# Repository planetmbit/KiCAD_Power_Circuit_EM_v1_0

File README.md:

# KiCAD_Power_Circuit_EM_v1_0
This is the Power Circuit of Private Satellite EM(Engineering Model)'s KiCAD Repository (This belongs to the author and The Ryman Sat Project.)

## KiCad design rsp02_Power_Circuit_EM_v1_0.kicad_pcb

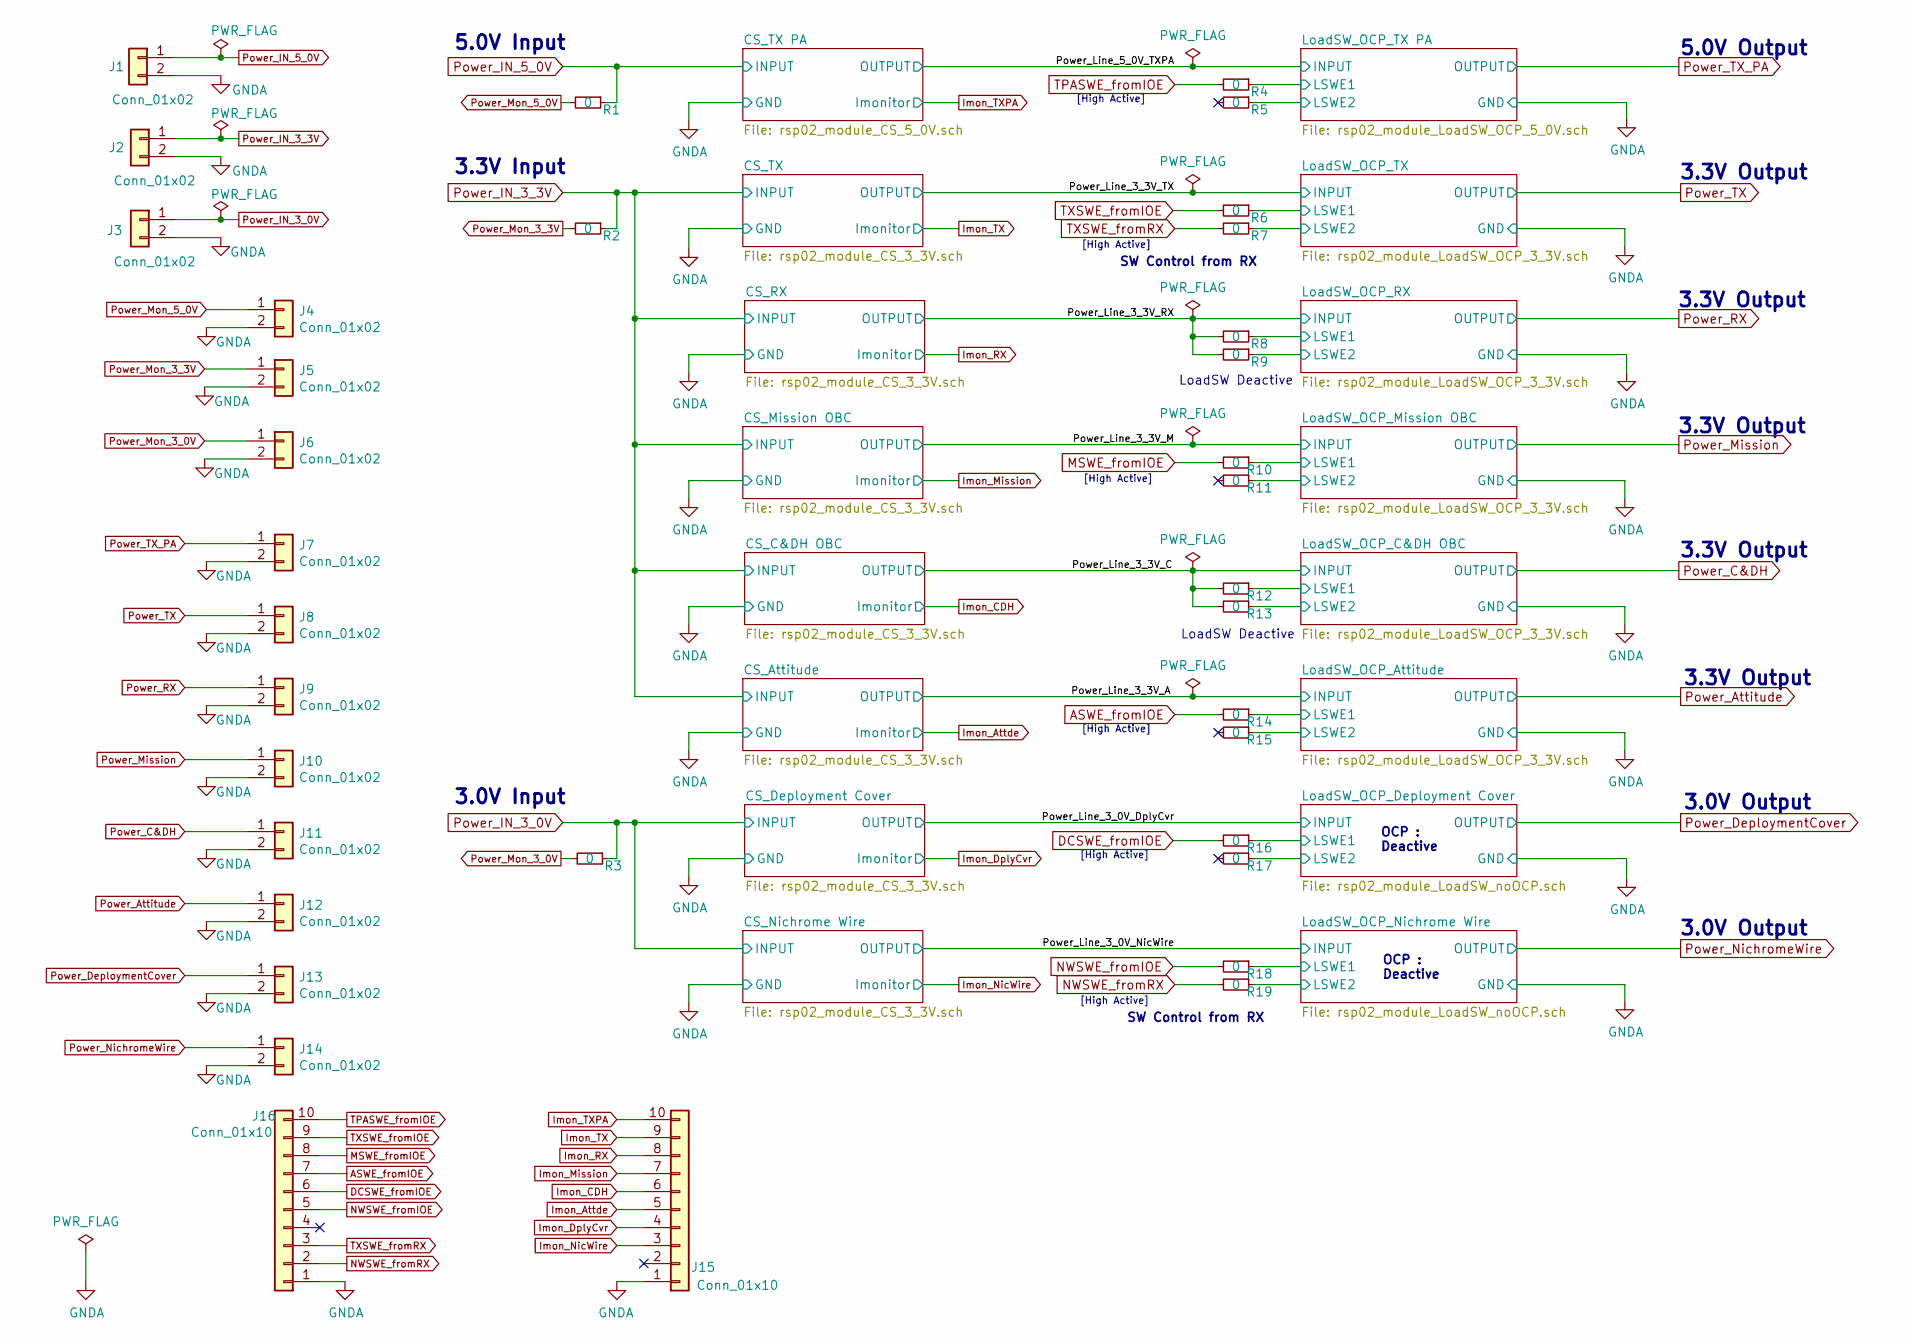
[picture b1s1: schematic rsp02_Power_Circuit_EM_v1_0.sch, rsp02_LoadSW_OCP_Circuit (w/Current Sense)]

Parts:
J1, J2, J3, J7, J8, J9, J10, J11, J12, J13, J14: Conn_01x02; TerminalBlock_Phoenix_MKDS-3-2-5.08_1x02_P5.08mm_Horizontal
J4, J5, J6: Conn_01x02; PinHeader_1x02_P2.54mm_Vertical
J15: Conn_01x10; PinHeader_1x10_P2.54mm_Vertical
J16: Conn_01x10; TerminalBlock_Phoenix_MKDS-3-10-5.08_1x10_P5.08mm_Horizontal
R1, R2, R3, R4, R5, R6, R7, R8, R9, R10, R11, R12, R13, R14, R15, R16, R17, R18, R19: 0; R_0603_1608Metric

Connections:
/LoadSW_OCP_Attitude/LSWE1: R14.1; also elsewhere on the board
/LoadSW_OCP_Attitude/LSWE2: R15.1; also elsewhere on the board
/LoadSW_OCP_C&DH OBC/LSWE1: R12.1; also elsewhere on the board
/LoadSW_OCP_C&DH OBC/LSWE2: R13.1; also elsewhere on the board
/LoadSW_OCP_Deployment Cover/LSWE1: R16.1; also elsewhere on the board
/LoadSW_OCP_Deployment Cover/LSWE2: R17.1; also elsewhere on the board
/LoadSW_OCP_Mission OBC/LSWE1: R10.1; also elsewhere on the board
/LoadSW_OCP_Mission OBC/LSWE2: R11.1; also elsewhere on the board
/LoadSW_OCP_Nichrome Wire/LSWE1: R18.1; also elsewhere on the board
/LoadSW_OCP_Nichrome Wire/LSWE2: R19.1; also elsewhere on the board
/LoadSW_OCP_RX/LSWE1: R8.1; also elsewhere on the board
/LoadSW_OCP_RX/LSWE2: R9.1; also elsewhere on the board
/LoadSW_OCP_TX PA/LSWE1: R4.1; also elsewhere on the board
/LoadSW_OCP_TX PA/LSWE2: R5.1; also elsewhere on the board
/LoadSW_OCP_TX/LSWE1: R6.1; also elsewhere on the board
/LoadSW_OCP_TX/LSWE2: R7.1; also elsewhere on the board
/Power_Line_3_3V_C: R12.2, R13.2; also elsewhere on the board
/Power_Line_3_3V_RX: R8.2, R9.2; also elsewhere on the board
ASWE_fromIOE: J16.7, R14.2
DCSWE_fromIOE: J16.6, R16.2
GNDA: J1.2, J2.2, J3.2, J4.2, J5.2, J6.2, J7.2, J8.2, J9.2, J10.2, J11.2, J12.2, J13.2, J14.2, J15.1, J16.1; also elsewhere on the board
Imon_Attde: J15.5; also elsewhere on the board
Imon_CDH: J15.6; also elsewhere on the board
Imon_DplyCvr: J15.4; also elsewhere on the board
Imon_Mission: J15.7; also elsewhere on the board
Imon_NicWire: J15.3; also elsewhere on the board
Imon_RX: J15.8; also elsewhere on the board
Imon_TX: J15.9; also elsewhere on the board
Imon_TXPA: J15.10; also elsewhere on the board
MSWE_fromIOE: J16.8, R10.2
NWSWE_fromIOE: J16.5, R18.2
NWSWE_fromRX: J16.2, R19.2
Power_Attitude: J12.1; also elsewhere on the board
Power_C&DH: J11.1; also elsewhere on the board
Power_DeploymentCover: J13.1; also elsewhere on the board
Power_IN_3_0V: J3.1, R3.1; also elsewhere on the board
Power_IN_3_3V: J2.1, R2.1; also elsewhere on the board
Power_IN_5_0V: J1.1, R1.1; also elsewhere on the board
Power_Mission: J10.1; also elsewhere on the board
Power_Mon_3_0V: J6.1, R3.2
Power_Mon_3_3V: J5.1, R2.2
Power_Mon_5_0V: J4.1, R1.2
Power_NichromeWire: J14.1; also elsewhere on the board
Power_RX: J9.1; also elsewhere on the board
Power_TX: J8.1; also elsewhere on the board
Power_TX_PA: J7.1; also elsewhere on the board
TPASWE_fromIOE: J16.10, R4.2
TXSWE_fromIOE: J16.9, R6.2
TXSWE_fromRX: J16.3, R7.2

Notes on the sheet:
5.0V Output
3.3V Output
OCP : Deactive
LoadSW Deactive
3.0V Output
SW Control from RX
[High Active]
3.0V Input
3.3V Input
5.0V Input

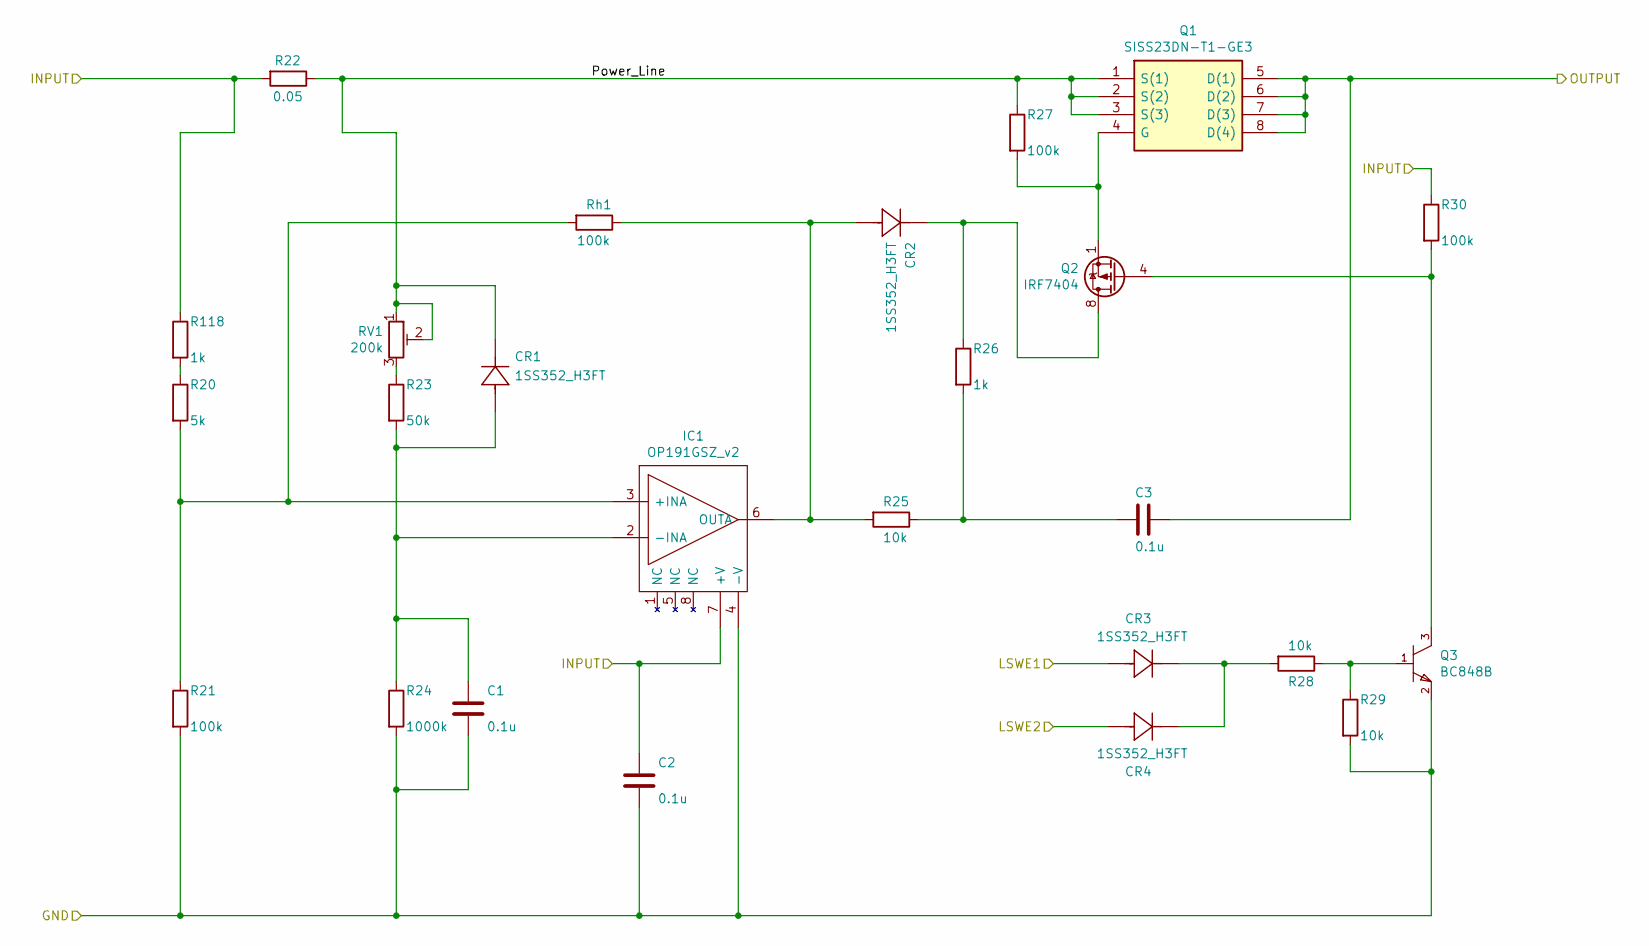
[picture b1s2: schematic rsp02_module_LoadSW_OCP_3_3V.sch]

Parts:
C16, C17, C18: 0.1u; C_0603_1608Metric
CR23, CR24, CR25, CR26: 1SS352_H3FT
IC6: OP191GSZ_v2; SOIC-8_3.9x4.9mm_P1.27mm; Manufacturer_Part_Number OP191GSZ
Q19: SISS23DN-T1-GE3; POWERPAK-1212-8; Manufacturer_Part_Number SISS23DN-T1-GE3
Q20: IRF7404; SOIC-8_3.9x4.9mm_P1.27mm
Q21: BC848B; SOT-23; mouser part number 771-BC848B215; digikey description TRANS NPN 30V 0.1A SOT23
R79: 5k; R_0603_1608Metric
R80, R86, R89: 100k; R_0603_1608Metric
R81: 0.05; R_2512_6332Metric
R82: 50k; R_0603_1608Metric
R83: 1000k; R_0603_1608Metric
R84, R87, R88: 10k; R_0603_1608Metric
R85, R123: 1k; R_0603_1608Metric
RV6: 200k; Potentiometer_Bourns_3314G_Vertical
Rh6: 100k; R_0603_1608Metric

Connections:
/LoadSW_OCP_TX/LSWE1: CR25.2 (anode); also elsewhere on the board
/LoadSW_OCP_TX/LSWE2: CR26.2 (anode); also elsewhere on the board
/LoadSW_OCP_TX/Power_Line: CR23.1 (cathode), Q19.1 (S(1)), Q19.2 (S(2)), Q19.3 (S(3)), R81.1, R86.1, RV6.1, RV6.2
/Power_Line_3_3V_TX: C17.1, IC6.7 (+V), R81.2, R89.1, R123.1; also elsewhere on the board
GNDA: C16.2, C17.2, IC6.4 (-V), Q21.2 (emitter), R80.2, R83.2, R88.2; also elsewhere on the board
unnamed: C16.1, CR23.2 (anode), IC6.2 (-INA), R82.2, R83.1
unnamed: C18.2, R84.1, R85.2
unnamed: CR24.1 (cathode), Q20.5 (D), Q20.6 (D), Q20.7 (D), Q20.8 (D), R85.1
unnamed: CR24.2 (anode), IC6.6 (OUTA), R84.2, Rh6.1
unnamed: CR25.1 (cathode), CR26.1 (cathode), R87.2
unnamed: IC6.3 (+INA), R79.2, R80.1, Rh6.2
unnamed: Q19.4 (G), Q20.1 (S), Q20.2 (S), Q20.3 (S), R86.2
unnamed: Q20.4 (G), Q21.3 (collector), R89.2
unnamed: Q21.1 (base), R87.1, R88.1
unnamed: R82.1, RV6.3
unnamed: R79.1, R123.2
Power_TX: C18.1, Q19.5 (D(1)), Q19.6 (D(2)), Q19.7 (D(3)), Q19.8 (D(4)); also elsewhere on the board

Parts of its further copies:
C1, C2, C3, C4, C5, C6, C7, C8, C9, C10, C11, C12: 0.1u; C_0603_1608Metric
CR1, CR2, CR3, CR4, CR5, CR6, CR7, CR8, CR9, CR10, CR11, CR12, CR13, CR14, CR15, CR16: 1SS352_H3FT
IC1, IC2, IC3, IC4: OP191GSZ_v2; SOIC-8_3.9x4.9mm_P1.27mm; Manufacturer_Part_Number OP191GSZ
Q1, Q4, Q7, Q10: SISS23DN-T1-GE3; POWERPAK-1212-8; Manufacturer_Part_Number SISS23DN-T1-GE3
Q2, Q5, Q8, Q11: IRF7404; SOIC-8_3.9x4.9mm_P1.27mm
Q3, Q6, Q9, Q12: BC848B; SOT-23; mouser part number 771-BC848B215; digikey description TRANS NPN 30V 0.1A SOT23
R20, R31, R42, R53: 5k; R_0603_1608Metric
R21, R27, R30, R32, R38, R41, R43, R49, R52, R54, R60, R63: 100k; R_0603_1608Metric
R22, R33, R44, R55: 0.05; R_2512_6332Metric
R23, R34, R45, R56: 50k; R_0603_1608Metric
R24, R35, R46, R57: 1000k; R_0603_1608Metric
R25, R28, R29, R36, R39, R40, R47, R50, R51, R58, R61, R62: 10k; R_0603_1608Metric
R26, R37, R48, R59, R118, R119, R120, R121: 1k; R_0603_1608Metric
RV1, RV2, RV3, RV4: 200k; Potentiometer_Bourns_3314G_Vertical
Rh1, Rh2, Rh3, Rh4: 100k; R_0603_1608Metric

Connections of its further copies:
/LoadSW_OCP_Attitude/LSWE1: CR15.2 (anode); also elsewhere on the board
/LoadSW_OCP_Attitude/LSWE2: CR16.2 (anode); also elsewhere on the board
/LoadSW_OCP_Attitude/Power_Line: CR13.1 (cathode), Q10.1 (S(1)), Q10.2 (S(2)), Q10.3 (S(3)), R55.1, R60.1, RV4.1, RV4.2
/LoadSW_OCP_C&DH OBC/LSWE1: CR11.2 (anode); also elsewhere on the board
/LoadSW_OCP_C&DH OBC/LSWE2: CR12.2 (anode); also elsewhere on the board
/LoadSW_OCP_C&DH OBC/Power_Line: CR9.1 (cathode), Q7.1 (S(1)), Q7.2 (S(2)), Q7.3 (S(3)), R44.1, R49.1, RV3.1, RV3.2
/LoadSW_OCP_Mission OBC/LSWE1: CR7.2 (anode); also elsewhere on the board
/LoadSW_OCP_Mission OBC/LSWE2: CR8.2 (anode); also elsewhere on the board
/LoadSW_OCP_Mission OBC/Power_Line: CR5.1 (cathode), Q4.1 (S(1)), Q4.2 (S(2)), Q4.3 (S(3)), R33.1, R38.1, RV2.1, RV2.2
/LoadSW_OCP_RX/LSWE1: CR3.2 (anode); also elsewhere on the board
/LoadSW_OCP_RX/LSWE2: CR4.2 (anode); also elsewhere on the board
/LoadSW_OCP_RX/Power_Line: CR1.1 (cathode), Q1.1 (S(1)), Q1.2 (S(2)), Q1.3 (S(3)), R22.1, R27.1, RV1.1, RV1.2
/Power_Line_3_3V_A: C11.1, IC4.7 (+V), R55.2, R63.1, R121.1; also elsewhere on the board
/Power_Line_3_3V_C: C8.1, IC3.7 (+V), R44.2, R52.1, R120.1; also elsewhere on the board
/Power_Line_3_3V_M: C5.1, IC2.7 (+V), R33.2, R41.1, R119.1; also elsewhere on the board
/Power_Line_3_3V_RX: C2.1, IC1.7 (+V), R22.2, R30.1, R118.1; also elsewhere on the board
GNDA: C1.2, C2.2, C4.2, C5.2, C7.2, C8.2, C10.2, C11.2, IC1.4 (-V), IC2.4 (-V), IC3.4 (-V), IC4.4 (-V), Q3.2 (emitter), Q6.2 (emitter), Q9.2 (emitter), Q12.2 (emitter), R21.2, R24.2, R29.2, R32.2, R35.2, R40.2, R43.2, R46.2, R51.2, R54.2, R57.2, R62.2; also elsewhere on the board
unnamed: C1.1, CR1.2 (anode), IC1.2 (-INA), R23.2, R24.1
unnamed: C3.2, R25.1, R26.2
unnamed: C4.1, CR5.2 (anode), IC2.2 (-INA), R34.2, R35.1
unnamed: C6.2, R36.1, R37.2
unnamed: C7.1, CR9.2 (anode), IC3.2 (-INA), R45.2, R46.1
unnamed: C9.2, R47.1, R48.2
unnamed: C10.1, CR13.2 (anode), IC4.2 (-INA), R56.2, R57.1
unnamed: C12.2, R58.1, R59.2
unnamed: CR2.1 (cathode), Q2.5 (D), Q2.6 (D), Q2.7 (D), Q2.8 (D), R26.1
unnamed: CR2.2 (anode), IC1.6 (OUTA), R25.2, Rh1.1
unnamed: CR3.1 (cathode), CR4.1 (cathode), R28.2
unnamed: CR6.1 (cathode), Q5.5 (D), Q5.6 (D), Q5.7 (D), Q5.8 (D), R37.1
unnamed: CR6.2 (anode), IC2.6 (OUTA), R36.2, Rh2.1
unnamed: CR7.1 (cathode), CR8.1 (cathode), R39.2
unnamed: CR10.1 (cathode), Q8.5 (D), Q8.6 (D), Q8.7 (D), Q8.8 (D), R48.1
unnamed: CR10.2 (anode), IC3.6 (OUTA), R47.2, Rh3.1
unnamed: CR11.1 (cathode), CR12.1 (cathode), R50.2
unnamed: CR14.1 (cathode), Q11.5 (D), Q11.6 (D), Q11.7 (D), Q11.8 (D), R59.1
unnamed: CR14.2 (anode), IC4.6 (OUTA), R58.2, Rh4.1
unnamed: CR15.1 (cathode), CR16.1 (cathode), R61.2
unnamed: IC1.3 (+INA), R20.2, R21.1, Rh1.2
unnamed: IC2.3 (+INA), R31.2, R32.1, Rh2.2
unnamed: IC3.3 (+INA), R42.2, R43.1, Rh3.2
unnamed: IC4.3 (+INA), R53.2, R54.1, Rh4.2
unnamed: Q1.4 (G), Q2.1 (S), Q2.2 (S), Q2.3 (S), R27.2
unnamed: Q2.4 (G), Q3.3 (collector), R30.2
unnamed: Q3.1 (base), R28.1, R29.1
unnamed: Q4.4 (G), Q5.1 (S), Q5.2 (S), Q5.3 (S), R38.2
unnamed: Q5.4 (G), Q6.3 (collector), R41.2
unnamed: Q6.1 (base), R39.1, R40.1
unnamed: Q7.4 (G), Q8.1 (S), Q8.2 (S), Q8.3 (S), R49.2
unnamed: Q8.4 (G), Q9.3 (collector), R52.2
unnamed: Q9.1 (base), R50.1, R51.1
unnamed: Q10.4 (G), Q11.1 (S), Q11.2 (S), Q11.3 (S), R60.2
unnamed: Q11.4 (G), Q12.3 (collector), R63.2
unnamed: Q12.1 (base), R61.1, R62.1
unnamed: R23.1, RV1.3
unnamed: R34.1, RV2.3
unnamed: R45.1, RV3.3
unnamed: R56.1, RV4.3
unnamed: R20.1, R118.2
unnamed: R31.1, R119.2
unnamed: R42.1, R120.2
unnamed: R53.1, R121.2
Power_Attitude: C12.1, Q10.5 (D(1)), Q10.6 (D(2)), Q10.7 (D(3)), Q10.8 (D(4)); also elsewhere on the board
Power_C&DH: C9.1, Q7.5 (D(1)), Q7.6 (D(2)), Q7.7 (D(3)), Q7.8 (D(4)); also elsewhere on the board
Power_Mission: C6.1, Q4.5 (D(1)), Q4.6 (D(2)), Q4.7 (D(3)), Q4.8 (D(4)); also elsewhere on the board
Power_RX: C3.1, Q1.5 (D(1)), Q1.6 (D(2)), Q1.7 (D(3)), Q1.8 (D(4)); also elsewhere on the board

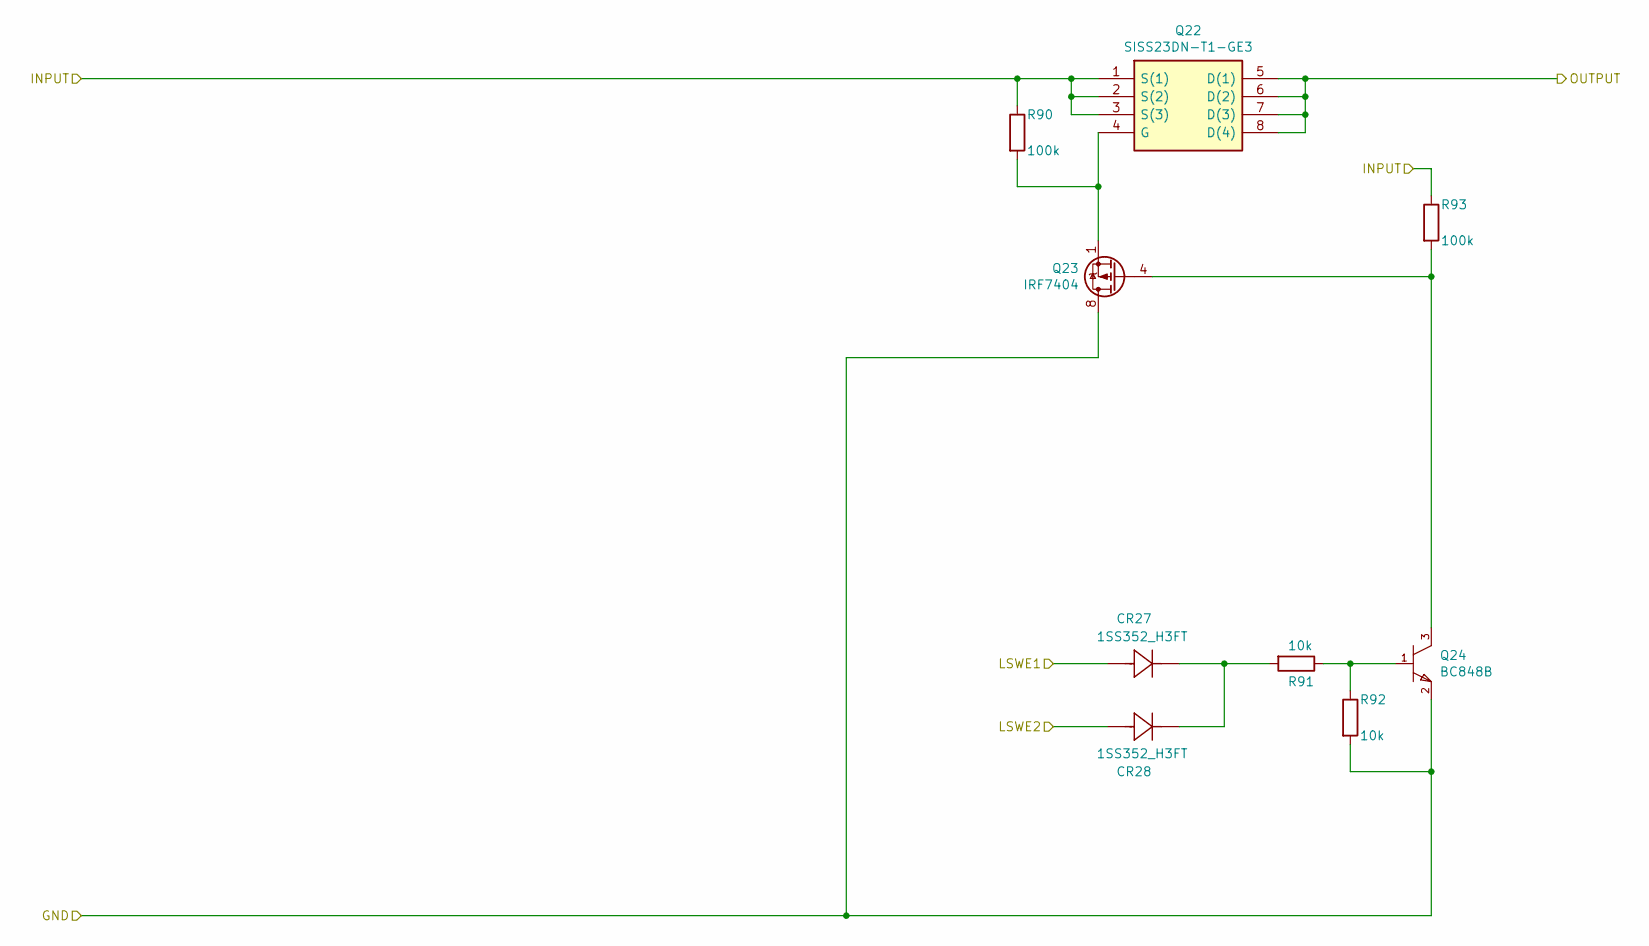
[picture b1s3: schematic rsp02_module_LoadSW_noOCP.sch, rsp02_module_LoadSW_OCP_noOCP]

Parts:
CR27, CR28: 1SS352_H3FT
Q22: SISS23DN-T1-GE3; POWERPAK-1212-8; Manufacturer_Part_Number SISS23DN-T1-GE3
Q23: IRF7404; SOIC-8_3.9x4.9mm_P1.27mm
Q24: BC848B; SOT-23; mouser part number 771-BC848B215; digikey description TRANS NPN 30V 0.1A SOT23
R90, R93: 100k; R_0603_1608Metric
R91, R92: 10k; R_0603_1608Metric

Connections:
/LoadSW_OCP_Deployment Cover/LSWE1: CR27.2 (anode); also elsewhere on the board
/LoadSW_OCP_Deployment Cover/LSWE2: CR28.2 (anode); also elsewhere on the board
/Power_Line_3_0V_DplyCvr: Q22.1 (S(1)), Q22.2 (S(2)), Q22.3 (S(3)), R90.1, R93.1; also elsewhere on the board
GNDA: Q23.5 (D), Q23.6 (D), Q23.7 (D), Q23.8 (D), Q24.2 (emitter), R92.2; also elsewhere on the board
unnamed: CR27.1 (cathode), CR28.1 (cathode), R91.2
unnamed: Q22.4 (G), Q23.1 (S), Q23.2 (S), Q23.3 (S), R90.2
unnamed: Q23.4 (G), Q24.3 (collector), R93.2
unnamed: Q24.1 (base), R91.1, R92.1
Power_DeploymentCover: Q22.5 (D(1)), Q22.6 (D(2)), Q22.7 (D(3)), Q22.8 (D(4)); also elsewhere on the board

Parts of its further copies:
CR17, CR18: 1SS352_H3FT
Q13: SISS23DN-T1-GE3; POWERPAK-1212-8; Manufacturer_Part_Number SISS23DN-T1-GE3
Q14: IRF7404; SOIC-8_3.9x4.9mm_P1.27mm
Q15: BC848B; SOT-23; mouser part number 771-BC848B215; digikey description TRANS NPN 30V 0.1A SOT23
R64, R67: 100k; R_0603_1608Metric
R65, R66: 10k; R_0603_1608Metric

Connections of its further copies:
/LoadSW_OCP_Nichrome Wire/LSWE1: CR17.2 (anode); also elsewhere on the board
/LoadSW_OCP_Nichrome Wire/LSWE2: CR18.2 (anode); also elsewhere on the board
/Power_Line_3_0V_NicWire: Q13.1 (S(1)), Q13.2 (S(2)), Q13.3 (S(3)), R64.1, R67.1; also elsewhere on the board
GNDA: Q14.5 (D), Q14.6 (D), Q14.7 (D), Q14.8 (D), Q15.2 (emitter), R66.2; also elsewhere on the board
unnamed: CR17.1 (cathode), CR18.1 (cathode), R65.2
unnamed: Q13.4 (G), Q14.1 (S), Q14.2 (S), Q14.3 (S), R64.2
unnamed: Q14.4 (G), Q15.3 (collector), R67.2
unnamed: Q15.1 (base), R65.1, R66.1
Power_NichromeWire: Q13.5 (D(1)), Q13.6 (D(2)), Q13.7 (D(3)), Q13.8 (D(4)); also elsewhere on the board

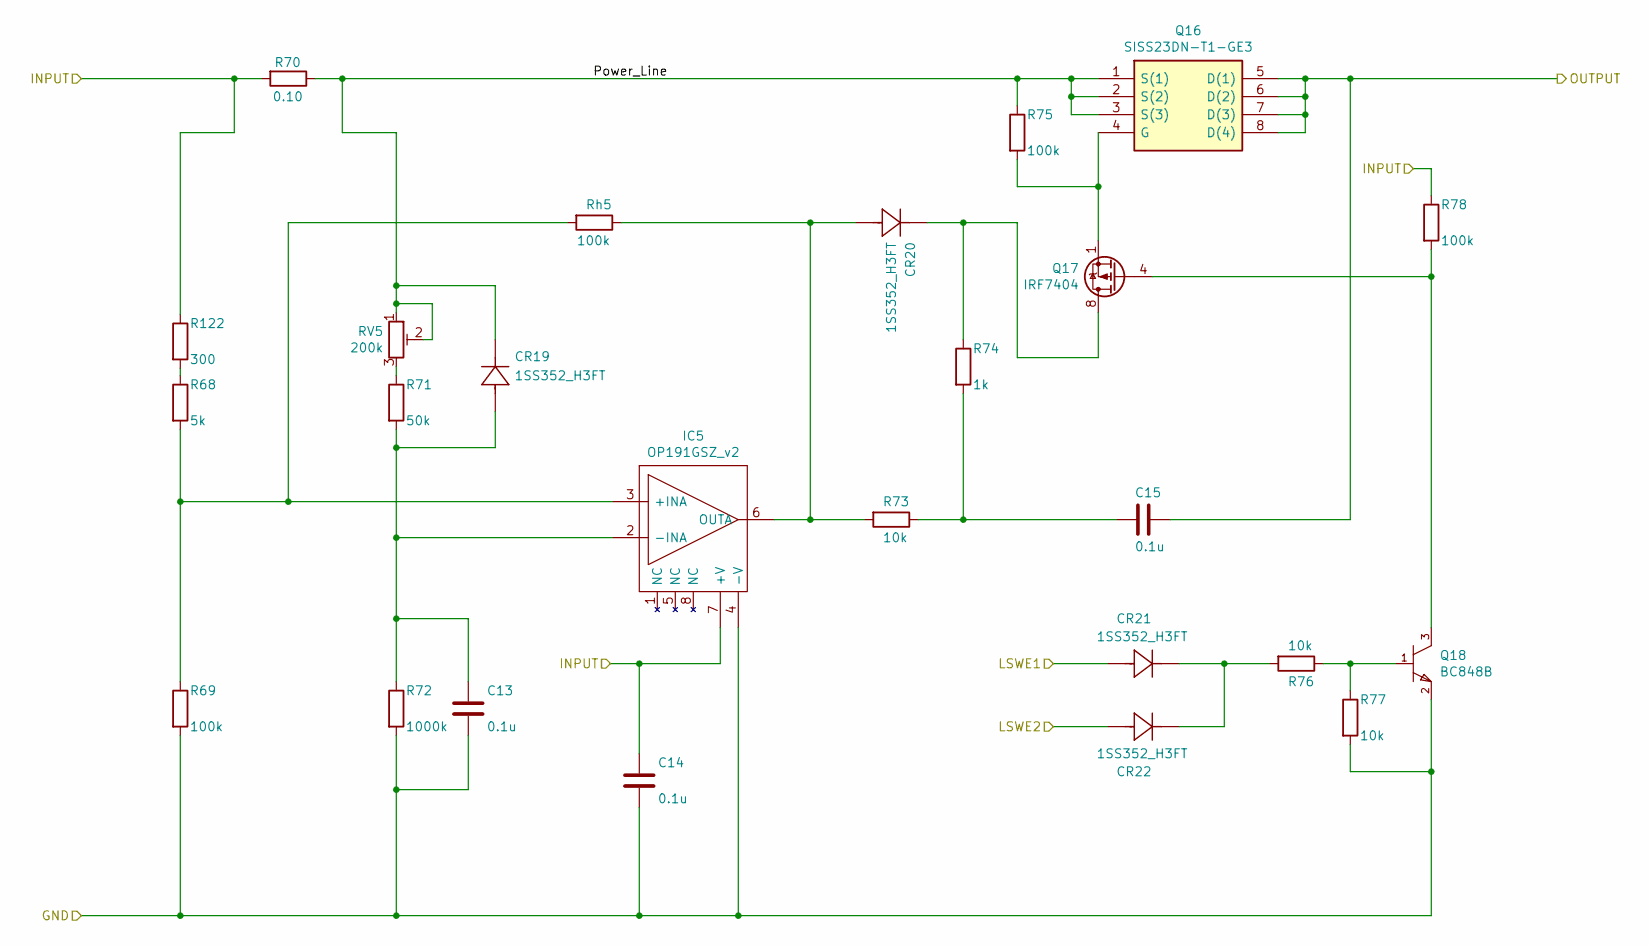
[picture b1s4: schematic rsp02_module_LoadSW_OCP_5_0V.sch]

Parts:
C13, C14, C15: 0.1u; C_0603_1608Metric
CR19, CR20, CR21, CR22: 1SS352_H3FT
IC5: OP191GSZ_v2; SOIC-8_3.9x4.9mm_P1.27mm; Manufacturer_Part_Number OP191GSZ
Q16: SISS23DN-T1-GE3; POWERPAK-1212-8; Manufacturer_Part_Number SISS23DN-T1-GE3
Q17: IRF7404; SOIC-8_3.9x4.9mm_P1.27mm
Q18: BC848B; SOT-23; mouser part number 771-BC848B215; digikey description TRANS NPN 30V 0.1A SOT23
R68: 5k; R_0603_1608Metric
R69, R75, R78: 100k; R_0603_1608Metric
R70: 0.10; R_2512_6332Metric
R71: 50k; R_0603_1608Metric
R72: 1000k; R_0603_1608Metric
R73, R76, R77: 10k; R_0603_1608Metric
R74: 1k; R_0603_1608Metric
R122: 300; R_0603_1608Metric
RV5: 200k; Potentiometer_Bourns_3314G_Vertical
Rh5: 100k; R_0603_1608Metric

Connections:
/LoadSW_OCP_TX PA/LSWE1: CR21.2 (anode); also elsewhere on the board
/LoadSW_OCP_TX PA/LSWE2: CR22.2 (anode); also elsewhere on the board
/LoadSW_OCP_TX PA/Power_Line: CR19.1 (cathode), Q16.1 (S(1)), Q16.2 (S(2)), Q16.3 (S(3)), R70.1, R75.1, RV5.1, RV5.2
/Power_Line_5_0V_TXPA: C14.1, IC5.7 (+V), R70.2, R78.1, R122.1; also elsewhere on the board
GNDA: C13.2, C14.2, IC5.4 (-V), Q18.2 (emitter), R69.2, R72.2, R77.2; also elsewhere on the board
unnamed: C13.1, CR19.2 (anode), IC5.2 (-INA), R71.2, R72.1
unnamed: C15.2, R73.1, R74.2
unnamed: CR20.1 (cathode), Q17.5 (D), Q17.6 (D), Q17.7 (D), Q17.8 (D), R74.1
unnamed: CR20.2 (anode), IC5.6 (OUTA), R73.2, Rh5.1
unnamed: CR21.1 (cathode), CR22.1 (cathode), R76.2
unnamed: IC5.3 (+INA), R68.2, R69.1, Rh5.2
unnamed: Q16.4 (G), Q17.1 (S), Q17.2 (S), Q17.3 (S), R75.2
unnamed: Q17.4 (G), Q18.3 (collector), R78.2
unnamed: Q18.1 (base), R76.1, R77.1
unnamed: R71.1, RV5.3
unnamed: R68.1, R122.2
Power_TX_PA: C15.1, Q16.5 (D(1)), Q16.6 (D(2)), Q16.7 (D(3)), Q16.8 (D(4)); also elsewhere on the board

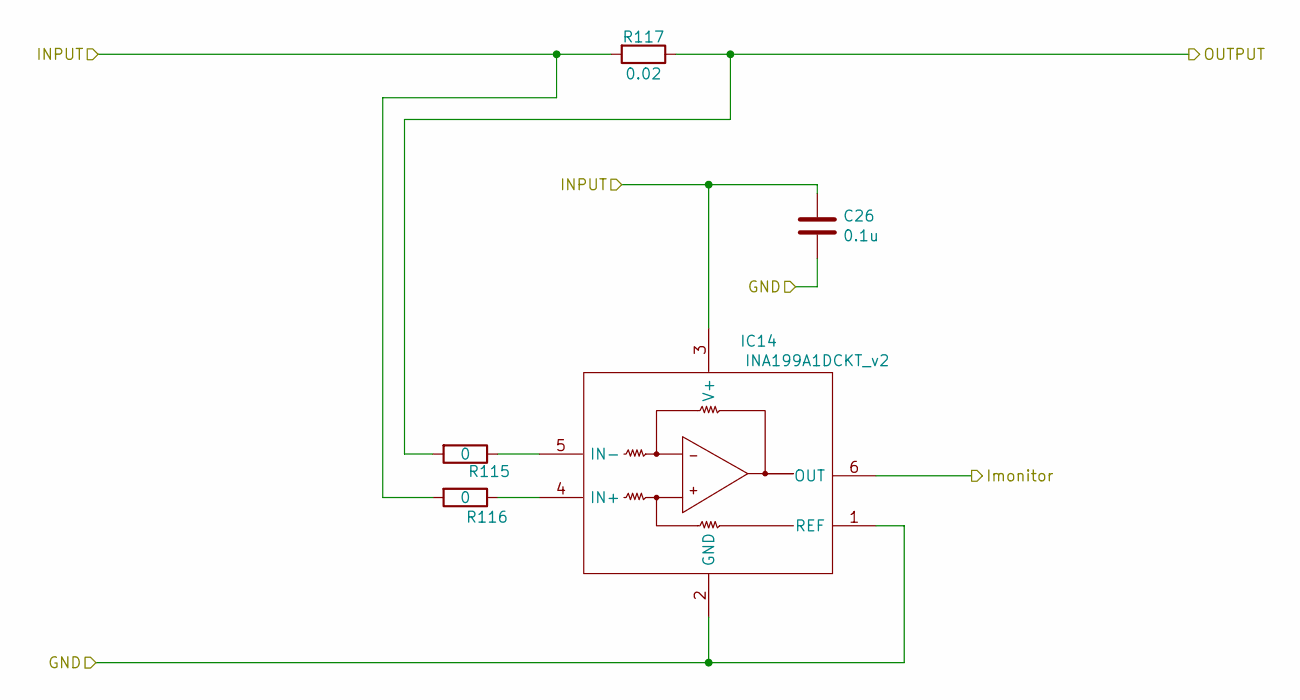
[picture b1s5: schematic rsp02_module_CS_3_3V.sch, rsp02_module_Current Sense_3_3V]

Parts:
C26: 0.1u; C_0603_1608Metric
IC14: INA199A1DCKT_v2; SOT-363_SC-70-6; Manufacturer_Part_Number INA199A1DCKT
R115, R116: 0; R_0603_1608Metric
R117: 0.02; R_2512_6332Metric

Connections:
/Power_Line_3_3V_TX: R115.2, R117.1; also elsewhere on the board
GNDA: C26.2, IC14.1 (REF), IC14.2 (GND); also elsewhere on the board
Imon_TX: IC14.6 (OUT); also elsewhere on the board
unnamed: IC14.4 (IN+), R116.1
unnamed: IC14.5 (IN-), R115.1
Power_IN_3_3V: C26.1, IC14.3 (V+), R116.2, R117.2; also elsewhere on the board

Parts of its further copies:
C19, C20, C21, C22, C23, C24: 0.1u; C_0603_1608Metric
IC7, IC8, IC9, IC10, IC11, IC12: INA199A1DCKT_v2; SOT-363_SC-70-6; Manufacturer_Part_Number INA199A1DCKT
R94, R95, R97, R98, R100, R101, R103, R104, R106, R107, R109, R110: 0; R_0603_1608Metric
R96, R99, R102, R105, R108, R111: 0.02; R_2512_6332Metric

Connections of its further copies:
/Power_Line_3_0V_DplyCvr: R97.2, R99.1; also elsewhere on the board
/Power_Line_3_0V_NicWire: R94.2, R96.1; also elsewhere on the board
/Power_Line_3_3V_A: R100.2, R102.1; also elsewhere on the board
/Power_Line_3_3V_C: R103.2, R105.1; also elsewhere on the board
/Power_Line_3_3V_M: R106.2, R108.1; also elsewhere on the board
/Power_Line_3_3V_RX: R109.2, R111.1; also elsewhere on the board
GNDA: C19.2, C20.2, C21.2, C22.2, C23.2, C24.2, IC7.1 (REF), IC7.2 (GND), IC8.1 (REF), IC8.2 (GND), IC9.1 (REF), IC9.2 (GND), IC10.1 (REF), IC10.2 (GND), IC11.1 (REF), IC11.2 (GND), IC12.1 (REF), IC12.2 (GND); also elsewhere on the board
Imon_Attde: IC9.6 (OUT); also elsewhere on the board
Imon_CDH: IC10.6 (OUT); also elsewhere on the board
Imon_DplyCvr: IC8.6 (OUT); also elsewhere on the board
Imon_Mission: IC11.6 (OUT); also elsewhere on the board
Imon_NicWire: IC7.6 (OUT); also elsewhere on the board
Imon_RX: IC12.6 (OUT); also elsewhere on the board
unnamed: IC7.4 (IN+), R95.1
unnamed: IC7.5 (IN-), R94.1
unnamed: IC8.4 (IN+), R98.1
unnamed: IC8.5 (IN-), R97.1
unnamed: IC9.4 (IN+), R101.1
unnamed: IC9.5 (IN-), R100.1
unnamed: IC10.4 (IN+), R104.1
unnamed: IC10.5 (IN-), R103.1
unnamed: IC11.4 (IN+), R107.1
unnamed: IC11.5 (IN-), R106.1
unnamed: IC12.4 (IN+), R110.1
unnamed: IC12.5 (IN-), R109.1
Power_IN_3_0V: C19.1, C20.1, IC7.3 (V+), IC8.3 (V+), R95.2, R96.2, R98.2, R99.2; also elsewhere on the board
Power_IN_3_3V: C21.1, C22.1, C23.1, C24.1, IC9.3 (V+), IC10.3 (V+), IC11.3 (V+), IC12.3 (V+), R101.2, R102.2, R104.2, R105.2, R107.2, R108.2, R110.2, R111.2; also elsewhere on the board

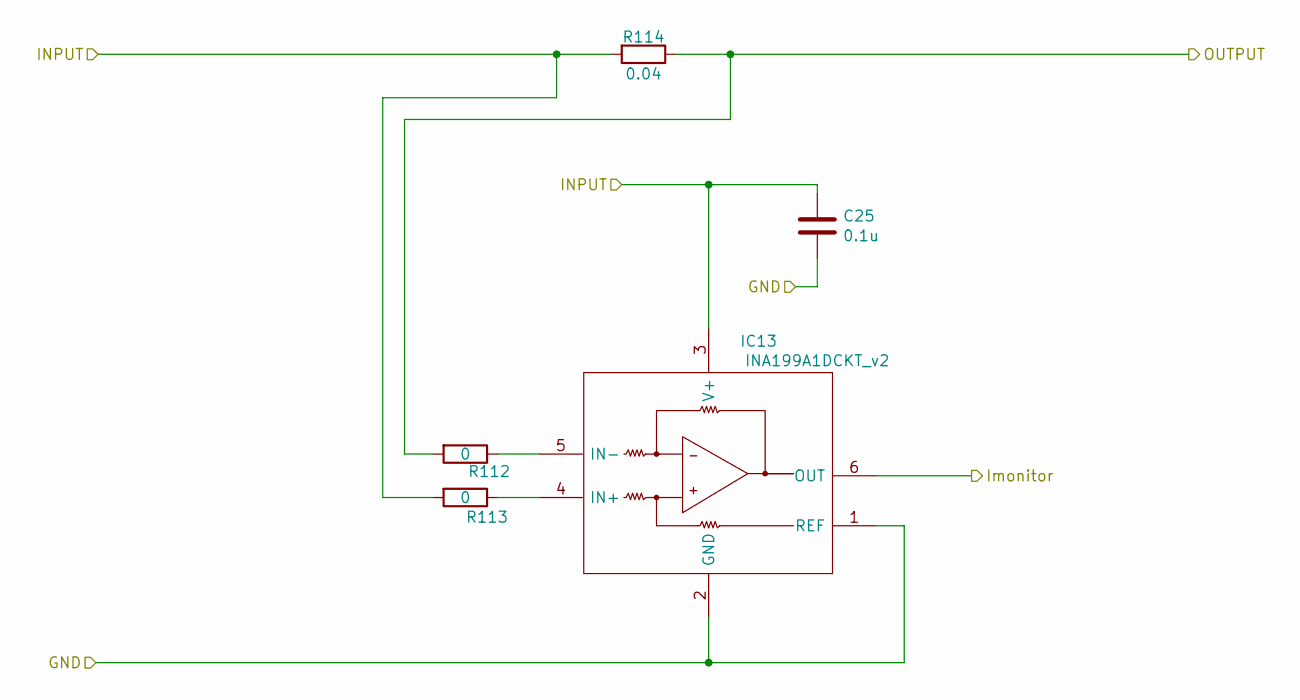
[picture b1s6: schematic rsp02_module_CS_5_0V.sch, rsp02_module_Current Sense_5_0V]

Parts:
C25: 0.1u; C_0603_1608Metric
IC13: INA199A1DCKT_v2; SOT-363_SC-70-6; Manufacturer_Part_Number INA199A1DCKT
R112, R113: 0; R_0603_1608Metric
R114: 0.04; R_2512_6332Metric

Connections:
/Power_Line_5_0V_TXPA: R112.2, R114.1; also elsewhere on the board
GNDA: C25.2, IC13.1 (REF), IC13.2 (GND); also elsewhere on the board
Imon_TXPA: IC13.6 (OUT); also elsewhere on the board
unnamed: IC13.4 (IN+), R113.1
unnamed: IC13.5 (IN-), R112.1
Power_IN_5_0V: C25.1, IC13.3 (V+), R113.2, R114.2; also elsewhere on the board
